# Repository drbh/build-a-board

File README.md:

# build-a-board

`bb` turns a small Rust program into a manufacturable KiCad board: it writes the `.kicad_pcb`, routes it, checks it, renders it, and packs the files JLCPCB asks for.

[the book](book/README.md) walks through a board from the first net to the release zip. try one in the browser at [bb.dholtz.com](https://bb.dholtz.com) with nothing installed; the book is there too, at [bb.dholtz.com/book](https://bb.dholtz.com/book/).

## install

with Rust installed through rustup:

```bash
git clone https://github.com/drbh/build-a-board.git
cargo install --path build-a-board
rustup target add wasm32-wasip2
bb doctor
```

`bb doctor` lists the tools `bb` calls and where it found them: `kicad-cli` and KiCad's footprint library, Java with the [FreeRouting](https://github.com/freerouting/freerouting) jar, and ImageMagick. set `KICAD_CLI`, `KICAD_FOOTPRINT_DIR`, `JAVA`, `FREEROUTING_JAR` or `MAGICK` to point at another install.

with nix, `nix develop` provides everything but KiCad on macOS, and `nix build` builds `bb`.

## a board

a board is a crate that depends on [`bb-sdk`](sdk) and returns one `Board` value. the smallest one, [examples/indicator](examples/indicator), is four LEDs on a header:

```bash
bb --board examples/indicator preview --watch --open   # draw it, redraw on every save
bb --board examples/indicator                          # generate, route, schematic, render
```

`--board` defaults to the current directory. the KiCad project and everything else `bb` makes land in `output/`.

read [a board, from nothing](book/01-a-board.md) to write your own, and the [reference](book/README.md#reference) for every command and builder.

## develop

```bash
cargo build --release          # target/release/bb
cargo test                     # builds the fixture boards for wasm32-wasip2
```

after editing anything in [`wit/`](wit), run `cargo run -p bb-sdk-bindgen` to regenerate the SDK's bindings; every board build fails with that message until you do.

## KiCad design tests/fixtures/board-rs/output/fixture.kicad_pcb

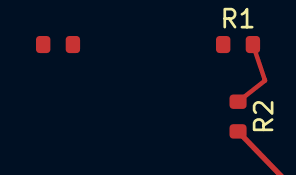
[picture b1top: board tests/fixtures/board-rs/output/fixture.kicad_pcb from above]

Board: 2 copper layers, 3 parts (0 on the bottom side), 3 nets.

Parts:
J1: IN; R_Test
R1, R2: 10k; R_Test

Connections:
GND: J1.2, R2.2
MID: R1.2, R2.1
VIN: J1.1, R1.1

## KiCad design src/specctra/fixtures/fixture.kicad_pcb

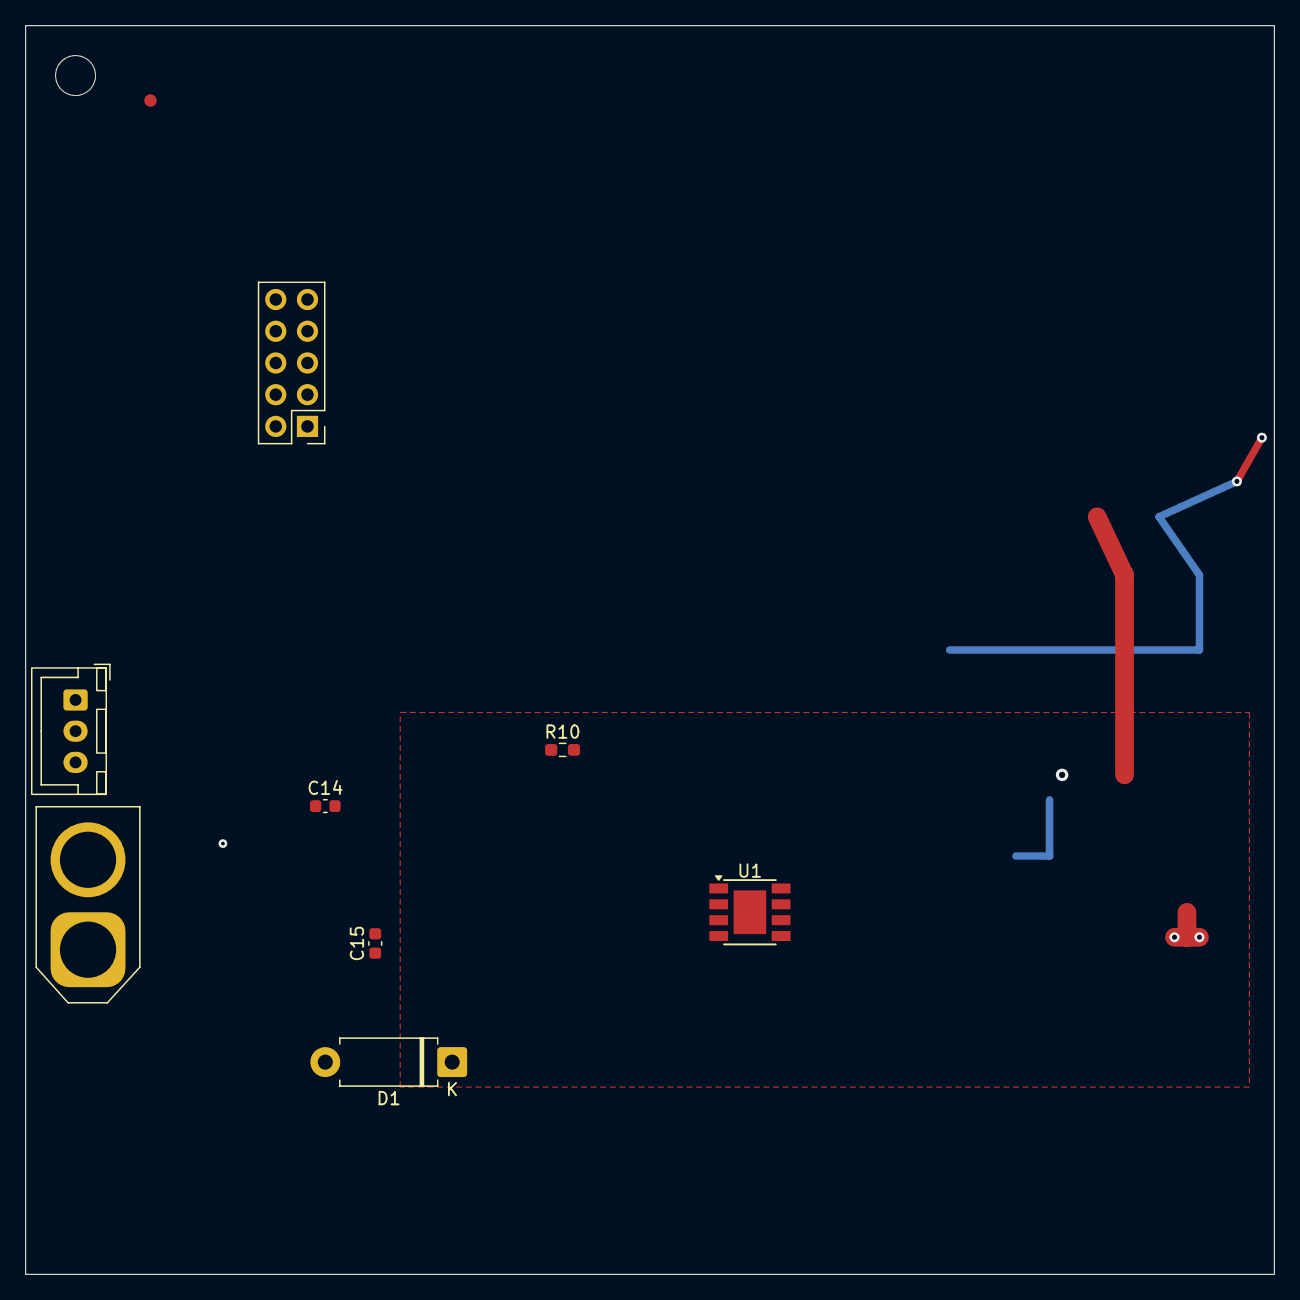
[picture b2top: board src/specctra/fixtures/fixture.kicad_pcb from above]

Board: 2 copper layers, 100.0 x 100.0 mm, 10 parts (0 on the bottom side), 2 nets.

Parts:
C14, C15: 100n 50V; C_0603_1608Metric
D1: P6KE22A; D_DO-15_P10.16mm_Horizontal
FID1: FIDUCIAL; Fiducial_1mm_Mask2mm
H1: M3; MountingHole_3.2mm_M3
J1: XT60-M PIGTAIL / 4S INPUT; AMASS_XT60-M_1x02_P7.20mm_Vertical
J9: SIMPLEFOC MINI V1.0 LEFT DIRECT CONTROL PINS; PinHeader_2x05_P2.54mm_Vertical
J16: LEFT MOTOR XH2.5; JST_XH_B3B-XH-A_1x03_P2.50mm_Vertical
R10: 4.7k; R_0603_1608Metric_Pad0.98x0.95mm_HandSolder
U1: AP64352SP-13; Diodes_SO-8EP

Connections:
GND: C15.1, D1.2, J1.1, J9.1, J9.4, U1.7, U1.9
VBAT: D1.1, U1.2, U1.3
